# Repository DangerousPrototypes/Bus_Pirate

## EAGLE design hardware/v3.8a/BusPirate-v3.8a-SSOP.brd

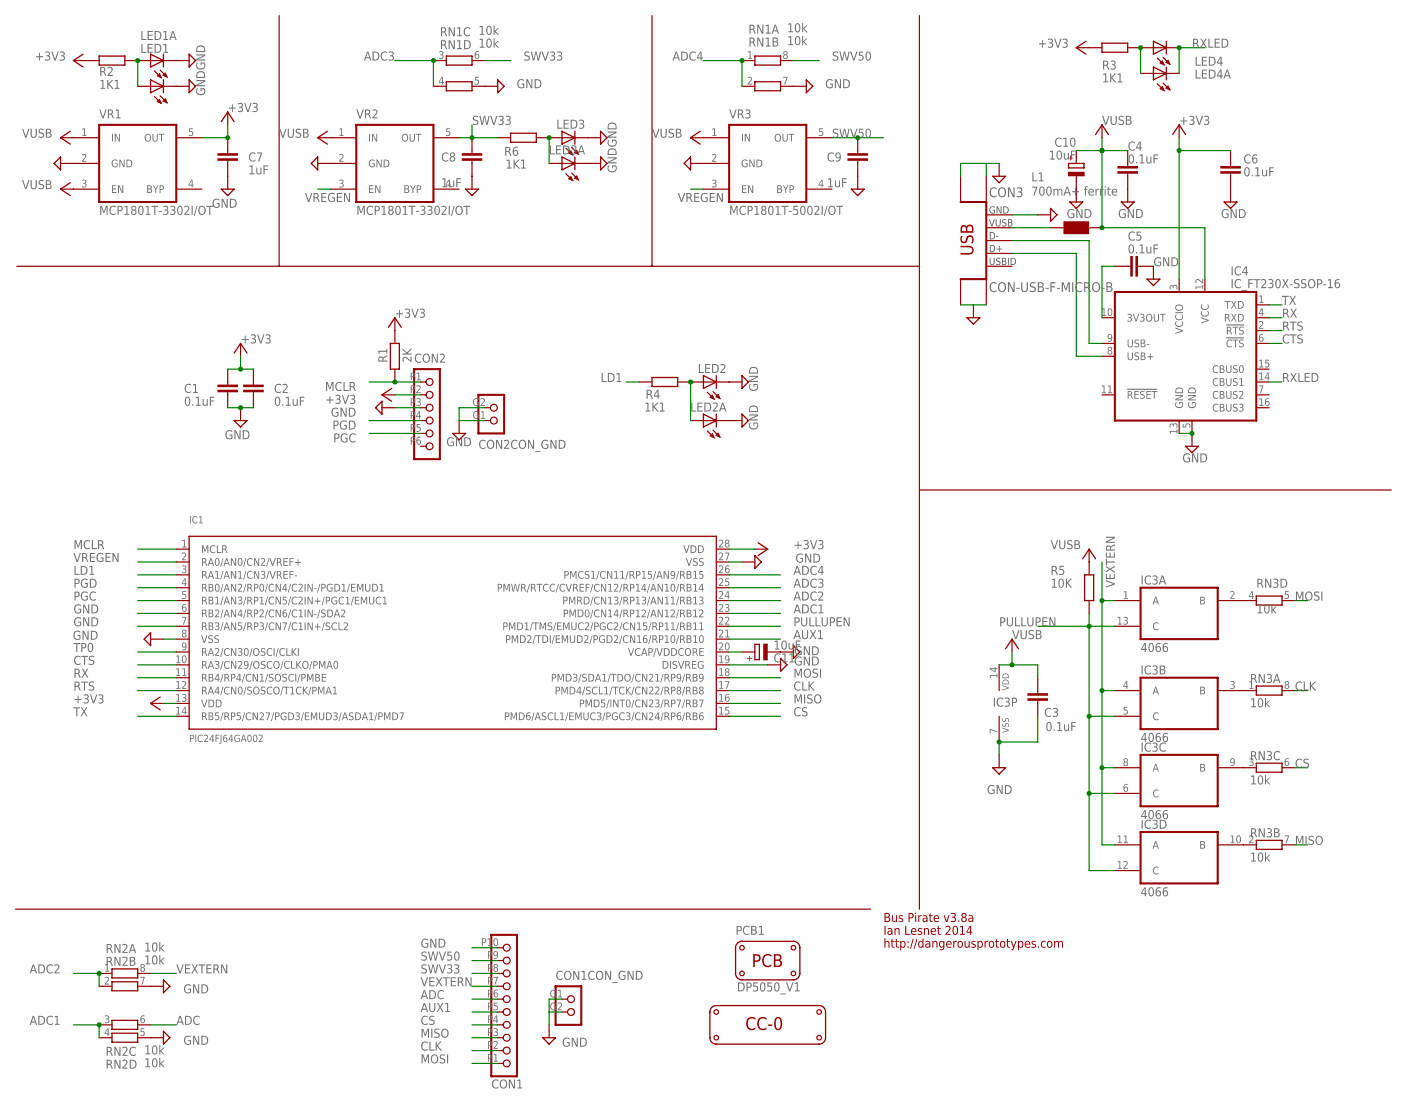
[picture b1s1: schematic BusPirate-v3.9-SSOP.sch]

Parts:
C1, C2, C3, C4, C5, C6: 0.1uF; C603
C7, C8, C9: 1uF; C603
C10, C11: 10uF; SMC_A
CON1: CON_JST_PH_10; CON_JST_PH_SMD_10
CON2: CON_JST_PH_6; CON_JST_PH_SMD_6
CON3: CON-USB-F-MICRO-B; CONN_USB_MICRO-B
IC1: PIC24FJ64GA002; SSOP28
IC3: 4066; TSSOP14
IC4: IC_FT230X-SSOP-16; SSOP-16-FTDI
L1: 700mA+ ferrite; WE-KI_0805_B
LED1, LED1A, LED2, LED2A, LED3, LED3A, LED4, LED4A: LED-0603; LED-603
LOGO1: LOGO_CC-0
PCB1: PCB_DP_SQUARE-5X5; DP5050_V1
R1: 2K; R603
R2, R3, R4, R6: 1K1; R603
R5: 10K; R603
RN1, RN2, RN3: 10k; RN8P-4R-CRA06S
VR1, VR2: MCP1801T-3302I/OT; SOT-23-5
VR3: MCP1801T-5002I/OT; SOT-23-5

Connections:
$N26: CON3.P1 (VUSB), L1.2 (1); also elsewhere on the board
+3V3: C1.1, C2.1, C6.1, C7.1, CON2.P2 (2), IC1.13 (VDD), IC1.28 (VDD), IC4.3 (VCCIO), R1.2, R2.2, R3.2, VR1.5 (OUT); also elsewhere on the board
ADC: CON1.P6 (6), RN2.6 (2); also elsewhere on the board
ADC1: IC1.23 (PMD0/CN14/RP12/AN12/RB12), RN2.3 (1), RN2.4 (1)
ADC2: IC1.24 (PMRD/CN13/RP13/AN11/RB13), RN2.1, RN2.2 (1)
ADC3: IC1.25 (PMWR/RTCC/CVREF/CN12/RP14/AN10/RB14), RN1.3 (1), RN1.4 (1)
ADC4: IC1.26 (PMCS1/CN11/RP15/AN9/RB15), RN1.1, RN1.2 (1)
AUX1: CON1.P5 (5), IC1.21 (PMD2/TDI/EMUD2/PGD2/CN16/RP10/RB10); also elsewhere on the board
CLK: CON1.P2 (2), IC1.17 (PMD4/SCL1/TCK/CN22/RP8/RB8), RN3.8 (2); also elsewhere on the board
CS: CON1.P4 (4), IC1.15 (PMD6/ASCL1/EMUC3/PGC3/CN24/RP6/RB6), RN3.6 (2); also elsewhere on the board
CTS: IC1.10 (RA3/CN29/OSCO/CLKO/PMA0), IC4.6 (!CTS)
GND: C1.2, C2.2, C3.2, C4.2, C5.2, C6.2, C7.2, C8.2, C9.2, C10.-, C11.-, CON1.G1 (1), CON1.G2 (2), CON1.P10 (10), CON2.G1 (1), CON2.G2 (2), CON2.P3 (3), CON3.BODY@1 (BODY), CON3.BODY@2 (BODY), CON3.BODY@3 (BODY), CON3.BODY@6 (BODY), CON3.P5 (GND), IC1.6 (RB2/AN4/RP2/CN6/C1IN-/SDA2), IC1.7 (RB3/AN5/RP3/CN7/C1IN+/SCL2), IC1.8 (VSS), IC1.19 (DISVREG), IC1.27 (VSS), IC3.7 (VSS), IC4.5 (GND), IC4.13 (GND), LED1.C, LED1A.C, LED2.C, LED2A.C, LED3.C, LED3A.C, RN1.5 (2), RN1.7 (2), RN2.5 (2), RN2.7 (2), VR1.2 (GND), VR2.2 (GND), VR3.2 (GND); also elsewhere on the board
LD1: IC1.3 (RA1/AN1/CN3/VREF-), R4.2
MCLR: CON2.P1 (1), IC1.1 (MCLR), R1.1; also elsewhere on the board
MISO: CON1.P3 (3), IC1.16 (PMD5/INT0/CN23/RP7/RB7), RN3.7 (2); also elsewhere on the board
MOSI: CON1.P1 (1), IC1.18 (PMD3/SDA1/TDO/CN21/RP9/RB9), RN3.5 (2); also elsewhere on the board
unnamed: IC3.2 (B), RN3.4 (1)
unnamed: IC3.9 (B), RN3.3 (1)
unnamed: C11.+, IC1.20 (VCAP/VDDCORE)
unnamed: IC3.10 (B), RN3.2 (1)
unnamed: IC3.3 (B), RN3.1
unnamed: LED2.A, LED2A.A, R4.1
unnamed: LED1.A, LED1A.A, R2.1
unnamed: C5.1, IC4.10 (3V3OUT)
unnamed: LED4.A, LED4A.A, R3.1
unnamed 25: CON3.P3 (D+), IC4.8 (USB+); also elsewhere on the board
unnamed 26: CON3.P2 (D-), IC4.9 (USB-); also elsewhere on the board
unnamed: LED3.A, LED3A.A, R6.1
PGC: CON2.P5 (5), IC1.5 (RB1/AN3/RP1/CN5/C2IN+/PGC1/EMUC1); also elsewhere on the board
PGD: CON2.P4 (4), IC1.4 (RB0/AN2/RP0/CN4/C2IN-/PGD1/EMUD1); also elsewhere on the board
PULLUPEN: IC1.22 (PMD1/TMS/EMUC2/PGC2/CN15/RP11/RB11), IC3.5 (C), IC3.6 (C), IC3.12 (C), IC3.13 (C), R5.2
RTS: IC1.12 (RA4/CN0/SOSCO/T1CK/PMA1), IC4.2 (!RTS)
RX: IC1.11 (RB4/RP4/CN1/SOSCI/PMBE), IC4.4 (RXD)
RXLED: IC4.14 (CBUS1), LED4.C, LED4A.C
SWV33: C8.1, CON1.P8 (8), R6.2, RN1.6 (2), VR2.5 (OUT); also elsewhere on the board
SWV50: C9.1, CON1.P9 (9), RN1.8 (2), VR3.5 (OUT); also elsewhere on the board
TP0: IC1.9 (RA2/CN30/OSCI/CLKI)
TX: IC1.14 (RB5/RP5/CN27/PGD3/EMUD3/ASDA1/PMD7), IC4.1 (TXD)
VEXTERN: CON1.P7 (7), IC3.1 (A), IC3.4 (A), IC3.8 (A), IC3.11 (A), RN2.8 (2); also elsewhere on the board
VREGEN: IC1.2 (RA0/AN0/CN2/VREF+), VR2.3 (EN), VR3.3 (EN)
VUSB: C3.1, C4.1, C10.+, IC3.14 (VDD), IC4.12 (VCC), L1.1 (2), R5.1, VR1.1 (IN), VR1.3 (EN), VR2.1 (IN), VR3.1 (IN)

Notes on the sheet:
Bus Pirate v3.8a
Ian Lesnet 2014
http://dangerousprototypes.com

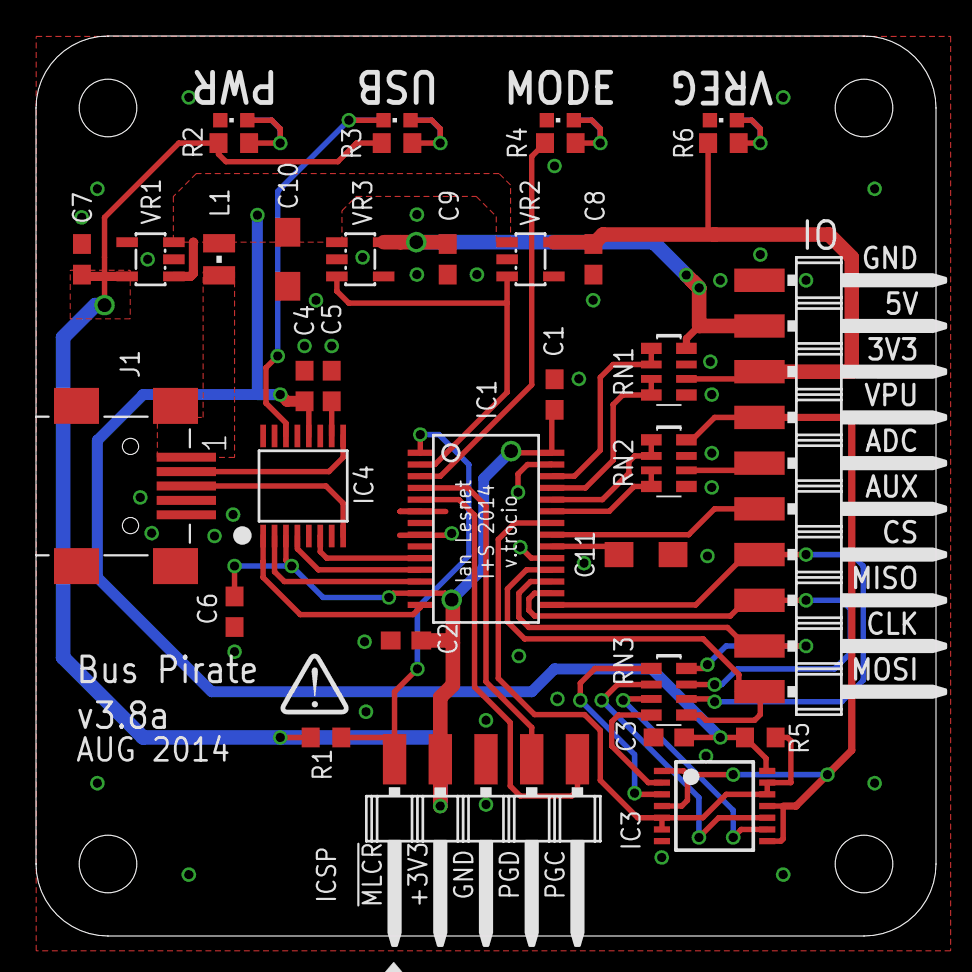
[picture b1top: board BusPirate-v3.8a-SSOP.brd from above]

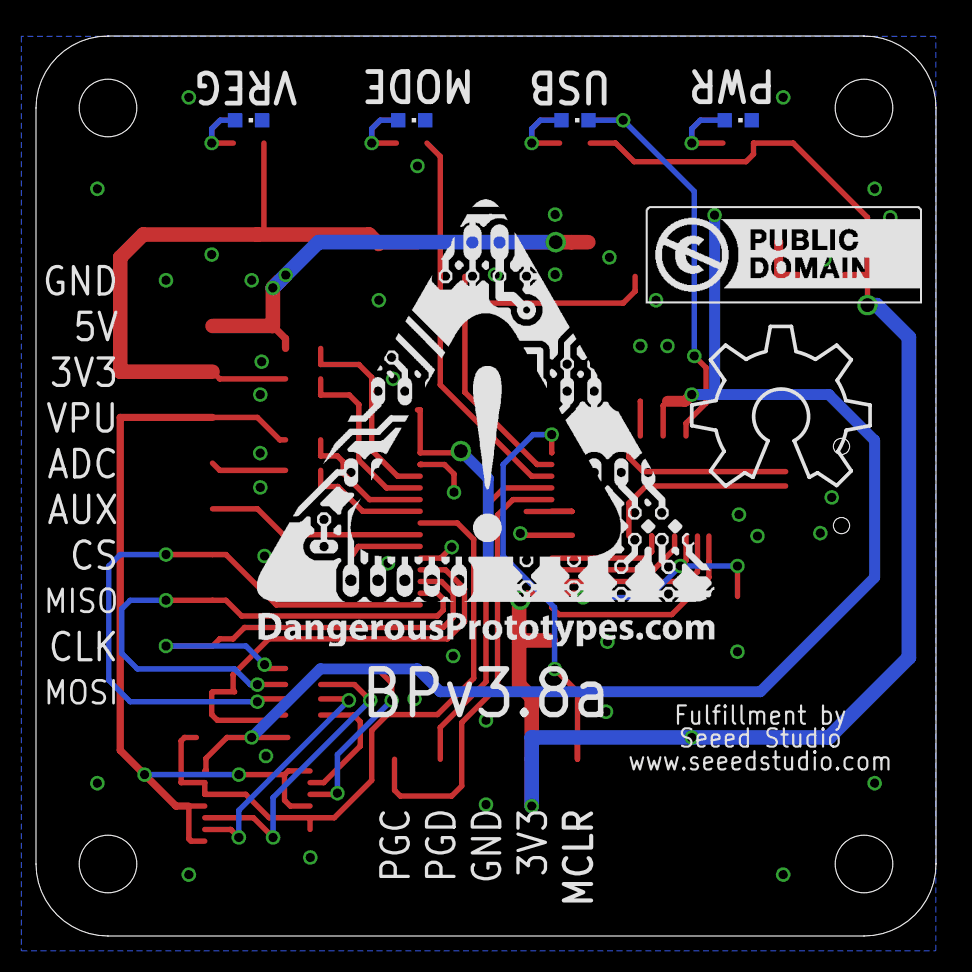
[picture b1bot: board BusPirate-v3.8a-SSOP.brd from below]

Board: 2 copper layers, 50.0 x 50.0 mm, 43 parts (7 on the bottom side), 40 nets.

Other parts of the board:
ICSP: CON_HEADER_1X05-SMD_RIGHT_ANGLED_MALE_B; M1X5_MALE_RIGHT_ANGLED_SMD_B
IO: CON_HEADER_1X10-_RIGHTANGLED_SMD; M1X10_MALE_RIGHT_ANGLED_SMD
J1: CON-USB-F-MINI-B; CONN_USB_MINI-B
U$1: DP-LOGO
U$2: OSHW_8X350_NOTEXT
U$3: DP_LOGO_ART_1X1

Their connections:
$N26: J1.VUSB; also elsewhere on the board
+3V3: ICSP.2; also elsewhere on the board
ADC: IO.5; also elsewhere on the board
AUX1: IO.6; also elsewhere on the board
CLK: IO.9; also elsewhere on the board
CS: IO.7; also elsewhere on the board
GND: ICSP.3, IO.1, J1.GND; also elsewhere on the board
MCLR: ICSP.1; also elsewhere on the board
MISO: IO.8; also elsewhere on the board
MOSI: IO.10; also elsewhere on the board
unnamed 25: J1.D+; also elsewhere on the board
unnamed 26: J1.D-; also elsewhere on the board
PGC: ICSP.5; also elsewhere on the board
PGD: ICSP.4; also elsewhere on the board
SWV33: IO.3; also elsewhere on the board
SWV50: IO.2; also elsewhere on the board
VEXTERN: IO.4; also elsewhere on the board
